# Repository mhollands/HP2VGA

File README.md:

# HP2VGA

Project to replace the display on the HP1662AS logic analyser with a VGA LCD display. 

The project uses a Texas Instruments TVP7002 Video ADC to digitise the video signal, a Lattice iCE40HX8K FPGA to buffer and upscale the video, and an Analog Devices ADV7125 to output the VGA signal to an LCD monitor.

Read more detail at projects.matthollands.com

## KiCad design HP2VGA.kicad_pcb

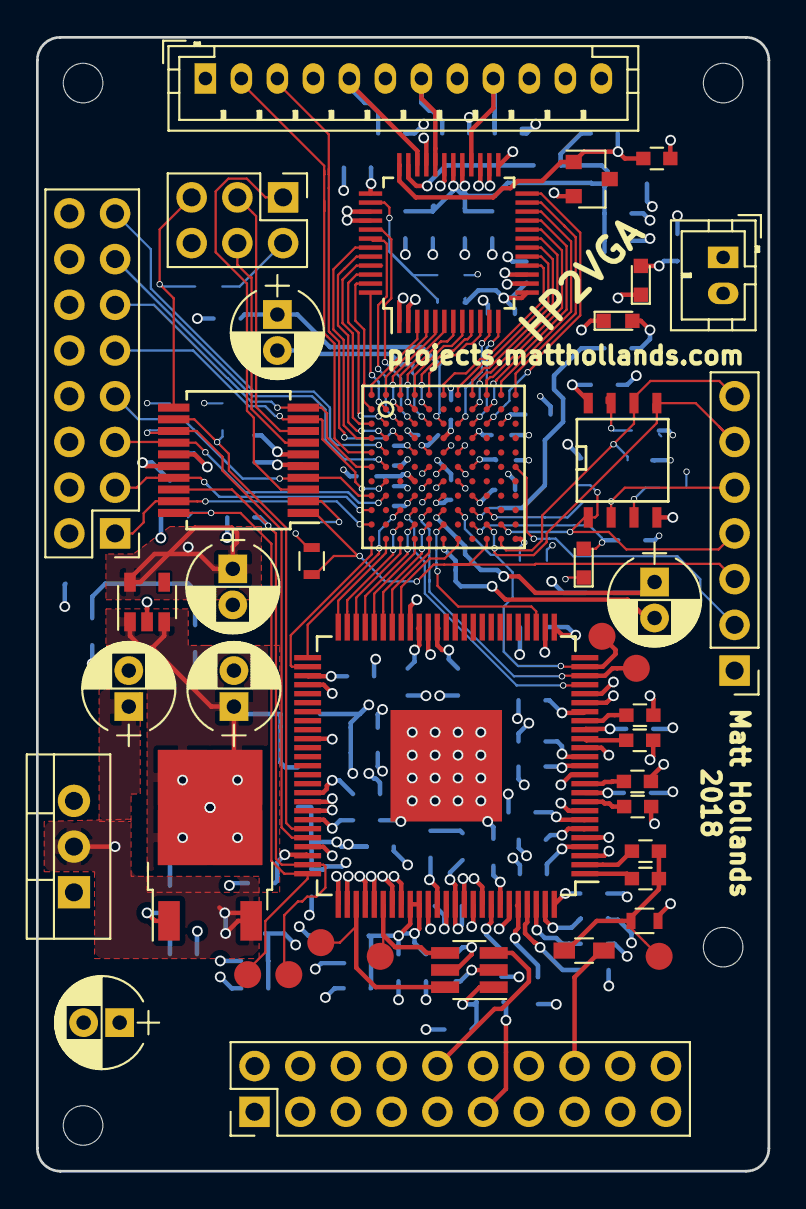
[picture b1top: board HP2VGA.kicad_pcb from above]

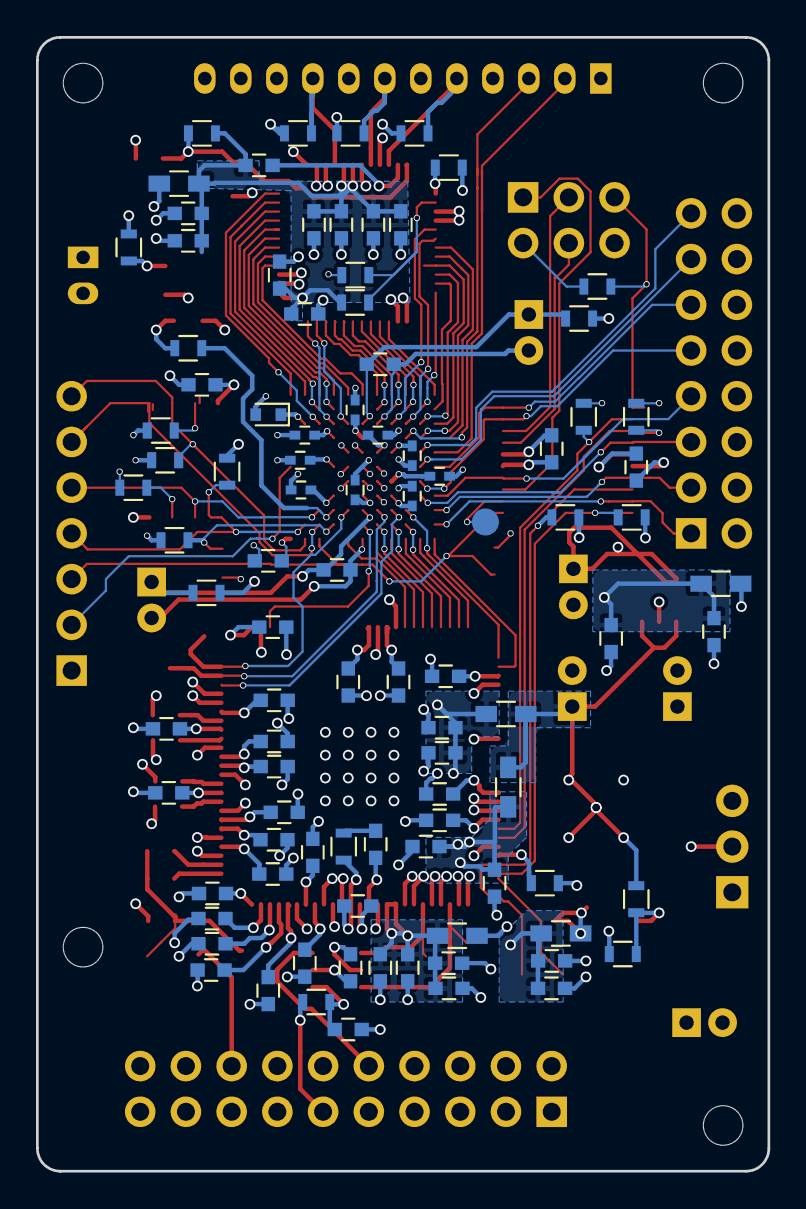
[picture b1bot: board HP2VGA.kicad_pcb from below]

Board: 4 copper layers, 40.6 x 63.0 mm, 141 parts (95 on the bottom side), 121 nets.

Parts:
C101, C102, C103, C104, C502, C504: 10uF; CP_Radial_D5.0mm_P2.00mm
C105, C107, C109, C111, C113, C115: 22uF; C_0603
C106, C108, C110, C112, C114, C116, C303: 1uF; C_0603
C201, C209: 1nF; C_0603
C202: 4.7nF; C_0603
C203, C205, C207, C208, C210, C211, C212, C213, C214, C215: 10nF; C_0603
C204: 10nf; C_0603
C206, C216, C217, C218, C219, C220, C221, C222, C223, C224, C225, C226, C227, C228, C229, C230, C231, C232, C233, C301, C304, C305, C306, C401, C402, C505, C506, C602: 0.1uF; C_0603
C302, C307, C308: 0.01uF; C_0603
C501, C503, C507, C508, C509, C510, C511, C512, C513: 0.1uF; C_0402
C601: 01uF; C_0603
CON101: AVR-ISP-6; Pin_Header_Straight_2x03_Pitch2.54mm
D101, D102, D501: LED; LED_0603
D502: CDBU0520; D_SOD-523
IC401: ATTINY87-AX; SSOP-20_5.3x7.2mm_Pitch0.65mm
L101, L102, L103, L104, L105, L106, L201: L_Small; R_0603_HandSoldering
P101: CONN_02X10; Pin_Header_Straight_2x10_Pitch2.54mm
P102: CONN_01X07; Pin_Header_Straight_1x07_Pitch2.54mm
P103: CONN_02X08; Pin_Header_Straight_2x08_Pitch2.54mm
P104: CONN_01X12; JST_PH_B12B-PH-K_12x2.00mm_Straight
P105: CONN_01X02; JST_PH_B2B-PH-K_02x2.00mm_Straight
P106, P107, P108, P109: CONN_01X01; MountingHole_2.2mm_M2
R101: 520; R_0603
R102, R302: 1k; R_0603
R103, R104: 0R; R_0603
R105, R106: 300R; R_0603
R201: 330; R_0603
R202: 75; R_0603
R203, R205, R208, R401, R402: 2k2; R_0603
R207: 1.5k; R_0603
R301: 530R; R_0603
R303, R304, R305: 75R; R_0603
R403: 4k7; R_0603
R501, R502: 100R; R_0603
R503: 649; R_0603
R504, R601, R602, R603, R604: 10k; R_0603
TP101, TP102: TEST; Measurement_Point_Round-SMD-Pad_Small
TP201: VIDEO; Measurement_Point_Round-SMD-Pad_Small
TP202: HSYNC; Measurement_Point_Round-SMD-Pad_Small
TP203: VSYNC; Measurement_Point_Round-SMD-Pad_Small
TP401: SERIAL_DEBUG; Measurement_Point_Round-SMD-Pad_Small
TP402: SDA; Measurement_Point_Round-SMD-Pad_Small
TP403: SCL; Measurement_Point_Round-SMD-Pad_Small
U101: LD1117V33; TO-220-3_Vertical
U102: NCP1117DTAG; TO-252-2
U103: TLV73312PDBVT; SOT-23-5
U201: SN74LVC2G17; SOT-23-6_Handsoldering
U202: TVP7002; TQFP-100_14x14mm_Pitch0.5mm-PowerPad
U301: ADV7125KSTZ50; LQFP-48_7x7mm_Pitch0.5mm
U302: AD1580ARTZ-REEL7; SOT-23
U501: iCE40HX8K-BG121; BGA-121-0.8mm
U601: Winbond W25Q80JV; SOIC-8-N

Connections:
+1V2: C104.1, C510.1, C511.1, C512.1, C513.1, R501.2, R502.2, U103.5, U501.D4, U501.D8, U501.H4, U501.H8
+1V9: C103.1, L101.1, L102.1, L103.1, R102.2, U102.2, U103.1, U103.3
+1V9A: C105.1, C106.1, C221.1, C222.1, C223.1, C224.1, L101.2, U202.4, U202.6, U202.7, U202.19
+1V9D: C109.1, C110.1, C219.1, C220.1, L103.2, U202.39, U202.69
+1V9PLL: C107.1, C108.1, C217.1, C218.1, L102.2, U202.84, U202.85
+3V3: C102.1, C401.1, C402.1, C501.1, C503.1, C507.1, C508.1, C509.1, C601.1, C602.1, CON101.2, D502.2, IC401.5, IC401.15, L104.1, L105.1, L106.1, R105.1, R401.1, R402.1, R403.2, R503.1, R504.1, R601.1, R602.2, R603.1, R604.1, U101.2, U102.3, U501.D6, U501.E4, U501.F8, U501.G4, U501.H6, U501.L11, U601.8
+3V3A0: C111.1, C112.1, C225.1, C226.1, C227.1, C228.1, C233.1, L104.2, U201.5, U202.13, U202.14, U202.93, U202.94
+3V3A1: C113.1, C114.1, C301.1, C302.1, C304.1, C305.1, C306.1, C307.1, C308.1, L105.2, R104.1, R302.1, U301.13, U301.29, U301.30
+3V3D0: C115.1, C116.1, C229.1, C230.1, C231.1, C232.1, L106.2, U202.26, U202.41, U202.53, U202.66
+12V: C101.1, P101.2, P101.5, P101.7, P101.9, P101.12, P105.2, U101.3
/FPGA/ADV_BLANK: U301.11, U501.C7
/FPGA/ADV_CLK: U301.24, U501.C9
/FPGA/ADV_SYNC: U301.12, U501.C8
/FPGA/B0: U301.16, U501.A6
/FPGA/B1: U301.17, U501.A7
/FPGA/B2: U301.18, U501.A8
/FPGA/B3: U301.19, U501.B8
/FPGA/B4: U301.20, U501.A9
/FPGA/B5: U301.21, U501.B9
/FPGA/B6: U301.22, U501.A10
/FPGA/B7: U301.23, U501.A11
/FPGA/CLK_EXT: P102.2, U501.F11
/FPGA/CLK_IN: U202.28, U501.K6
/FPGA/DEBUG6: P103.13, U501.F2
/FPGA/DEBUG7: P103.15, U501.E2
/FPGA/DONE: D501.2, R503.2, U501.K8
/FPGA/FIDOUT_IN: U202.22, U501.J4
/FPGA/FRAME_LED: R106.1, U501.J8
/FPGA/G0: U301.3, U501.A1
/FPGA/G1: U301.4, U501.A2
/FPGA/G2: U301.5, U501.B3
/FPGA/G3: U301.6, U501.A3
/FPGA/G4: U301.7, U501.B4
/FPGA/G5: U301.8, U501.A4
/FPGA/G6: U301.9, U501.B5
/FPGA/G7: U301.10, U501.A5
/FPGA/HSYNC_IN: TP101.1, U202.24, U501.J7
/FPGA/PROG_SCK: P102.7, R601.2, U501.L10, U601.6
/FPGA/PROG_SDI: P102.5, U501.J9, U601.2
/FPGA/PROG_SDO: P102.6, U501.K9, U601.5
/FPGA/PROG_SS: P102.4, R603.2, U501.K10, U601.1
/FPGA/R0: U301.41, U501.C4
/FPGA/R1: U301.42, U501.C3
/FPGA/R2: U301.43, U501.D1
/FPGA/R3: U301.44, U501.D2
/FPGA/R4: U301.45, U501.C1
/FPGA/R5: U301.46, U501.C2
/FPGA/R6: U301.47, U501.B1
/FPGA/R7: U301.48, U501.B2
/FPGA/VSYNC_IN: TP102.1, U202.23, U501.J5
/HSYNC_IN_A: P101.10, U201.3
/RX/G_0: U202.52, U501.L1
/RX/G_1: U202.51, U501.J3
/RX/G_2: U202.50, U501.L2
/RX/G_3: U202.49, U501.K3
/RX/G_4: U202.48, U501.L3
/RX/G_5: U202.47, U501.K4
/RX/G_6: U202.46, U501.L4
/RX/G_7: U202.45, U501.K5
/RX/G_8: U202.44, U501.L5
/RX/G_9: U202.43, U501.L7
/RX/HSYNC_BUFF: TP202.1, U201.4, U202.81
/RX/I2C_SCL: IC401.18, R402.2, TP403.1, U202.74
/RX/I2C_SDA: IC401.20, R401.2, TP402.1, U202.75
/RX/TVP_PWDN: IC401.12, R205.1, U202.70
/RX/TVP_RESET: IC401.13, R203.1, U202.71
/RX/VIDEO_L: C206.2, C209.2, L201.2, R202.1, TP201.1
/RX/VSYNC_BUFF: TP203.1, U201.6, U202.78
/TX/BLUE: P104.9, R305.1, U301.28
/TX/GREEN: P104.7, R304.1, U301.32
/TX/HSYNC_IN: P104.3, U501.D3
/TX/PSAVE: R103.2, R104.2, U301.38
/TX/RED: P104.5, R303.1, U301.34
/TX/VSYNC_IN: P104.2, U501.E1
/TX/Vref: C303.1, R302.2, U301.36, U302.1
/VIDEO_IN: L201.1, P101.16
/VSYNC_IN_A: P101.11, R201.2
/uC/FPGA_FB0: IC401.19, P103.1, U501.K1
/uC/FPGA_FB1: IC401.17, P103.3, U501.J1
/uC/FPGA_FB2: IC401.14, P103.5, U501.H2
/uC/FPGA_FB3: IC401.4, P103.7, U501.H1
/uC/FPGA_FB4: IC401.9, P103.9, U501.G2
/uC/FPGA_FB5: IC401.10, P103.11, U501.F1
/uC/FPGA_RESET: IC401.1, P102.3, R504.2, U501.L9
/uC/ISP_MISO: CON101.1, IC401.3
/uC/ISP_MOSI: CON101.4, IC401.7
/uC/ISP_RESET: CON101.5, IC401.11, R403.1
/uC/ISP_SCK: CON101.3, IC401.8
GND: C101.2, C102.2, C103.2, C104.2, C105.2, C106.2, C107.2, C108.2, C109.2, C110.2, C111.2, C112.2, C113.2, C114.2, C115.2, C116.2, C201.2, C203.2, C204.2, C205.2, C207.2, C208.2, C210.2, C211.2, C212.2, C213.2, C214.2, C215.2, C217.2, C218.2, C219.2, C220.2, C221.2, C222.2, C223.2, C224.2, C225.2, C226.2, C227.2, C228.2, C229.2, C230.2, C231.2, C232.2, C233.2, C301.2, C302.2, C303.2, C305.2, C306.2, C307.2, C308.2, C401.2, C402.2, C501.2, C503.2, C507.2, C508.2, C509.2, C510.2, C511.2, C512.2, C513.2, C601.2, C602.2, CON101.6, D101.1, D102.1, D501.1, IC401.6, IC401.16, P101.3, P101.4, P101.6, P101.8, P101.13, P101.14, P101.15, P101.17, P101.19, P102.1, P103.2, P103.4, P103.6, P103.8, P103.10, P103.12, P103.14, P103.16, P104.1, P104.4, P104.6, P104.8, P104.10, P105.1, P106.1, P107.1, P108.1, P109.1, R101.2, R103.1, R202.2, R203.2, R205.2, R208.2, R301.1, R303.2, R304.2, R305.2, U101.1, U103.2, U201.2, U202.3, U202.5, U202.8, U202.12, U202.15, U202.20, U202.21, U202.27, U202.40, U202.42, U202.54, U202.60, U202.67, U202.68, U202.72, U202.76, U202.77, U202.79, U202.80, U202.82, U202.83, U202.86, U202.90, U202.91, U202.92, U202.95, U202.101, U301.1, U301.2, U301.14, U301.15, U301.25, U301.26, U301.27, U301.31, U301.33, U301.39, U301.40, U302.2, U501.E5, U501.E6, U501.E7, U501.F5, U501.F6, U501.F7, U501.G5, U501.G6, U501.G7, U501.H5, U601.4
unnamed: C201.1, R201.1, U201.1
unnamed: C202.1, U202.88
unnamed: C202.2, R207.2, U202.89
unnamed: C203.1, U202.9
unnamed: C204.1, U202.11
unnamed: C205.1, U202.98
unnamed: C206.1, U202.2
unnamed: C207.1, U202.17
unnamed: C208.1, U202.97
unnamed: C209.1, U202.1
unnamed: C210.1, U202.10
unnamed: C211.1, U202.96
unnamed: C212.1, U202.100
unnamed: C213.1, U202.16
unnamed: C214.1, U202.18
unnamed: C215.1, U202.99
unnamed: C216.1, U202.87
unnamed: C216.2, R207.1
unnamed: C304.2, U301.35
unnamed: C502.1, C505.1, R501.1, U501.J6
unnamed: C502.2, C505.2, U501.L6
unnamed: C504.1, C506.1, R502.1, U501.C6
unnamed: C504.2, C506.2, U501.C5
unnamed: D101.2, R105.2
unnamed: D102.2, R106.2
unnamed: D502.1, U501.C10
unnamed: IC401.2, TP401.1
unnamed: R101.1, R102.1, U102.1
unnamed: R208.1, U202.73
unnamed: R301.2, U301.37
unnamed: R602.1, U601.3
unnamed: R604.2, U601.7

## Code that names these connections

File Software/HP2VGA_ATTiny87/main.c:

/*
 * HP2VGA_ATTiny87.c
 *
 * Created: 29/08/2018 21:21:04
 * Author : Matt
 */ 

#define F_CPU 8000000U

#include <stdbool.h>
#include <avr/io.h>
#include <util/delay.h>
#include <avr/interrupt.h>
#include "usiTwiMaster.h"

void TVP_PWDN(bool);
void TVP_RESET(bool);

#define TVP_W 0xB8
#define TVP_R 0xB9
#define TVP_CHIP_REV 0x00
#define TVP_HPLL_DIV_MSB 0x01
#define TVP_HPLL_DIV_LSB 0x02
#define TVP_HPLL_CTRL 0x03
#define TVP_HPLL_PHASE 0x04
#define TVP_CLAMP_START 0x05
#define TVP_CLAMP_WIDTH 0x06
#define TVP_GREEN_FINE_OFFSET 0x0C
#define TVP_SYNC_CTRL1 0x0E
#define TVP_HPLL_PRECOAST 0x12
#define TVP_SYNC_DETECT_STATUS 0x14
#define TVP_MISC_CTRL2 0x17
#define TVP_MISC_CTRL3 0x18
#define TVP_MISC_CTRL4 0x22
#define TVP_ALC_EN 0x26
#define TVP_POWER_CTRL 0x2B
#define TVP_SYNC_BYPASS 0x36
#define TVP_LPFl_STATUS 0x37
#define TVP_LPFh_STATUS 0x38
#define TVP_CPLl_STATUS 0x39
#define TVP_CPLh_STATUS 0x3A
#define TVP_HSYNC_WIDTH 0x3B
#define TVP_VSYNC_WIDTH 0x3C
#define TVP_1ST_COEF 0x4A

//800 pixels per line. hsync is 64. FP is 136. BP is 24.
//417 lines per frame. vsync is 3. FP is 25. BP is 11.
uint8_t reg_setting[66] = {	TVP_W, 0x00, 0x00, 0x64, 0x00, 0x20, 0x11, 0x01, 0x30, 0x51, 0x00, 0x90, 0x00, 0x40, 0x78, 0x80, 0x52, 0x2E, 0x5D, 0x20, 0x03, 0x03, 0x00, 0x04, 0x11,
							0x12, 0x01, 0x00, 0xC2, 0x87, 0x07, 0x00, 0x10, 0x10, 0x10, 0x00, 0x06, 0x00, 0x00, 0x00, 0x00, 0x00, 0x53, 0x08, 0x07, 0x85, 0x50, 0x00,
							0x80, 0x8c, 0x04, 0x18, 0x18, 0x60, 0x03, 0x10, 0x00, 0x00, 0x00, 0x00, 0x00, 0x00, 0x00, 0x03, 0x04, 0x0F};

//uint8_t reg_setting[66] = {	TVP_W, 0x00, 0x00, 0x64, 0x00, 0x20, 0x01, 0x01, 0x30, 0x51, 0x00, 0x90, 0x00, 0./x40, 0x78, 0x80, 0x52, 0x2E, 0x5D, 0x20, 0x03, 0x03, 0x00, 0x04, 0x11,
//	0x12, 0x01, 0x00, 0xC2, 0x87, 0x07, 0x00, 0x10, 0x10, 0x10, 0x00, 0x06, 0x00, 0x00, 0x00, 0x00, 0x00, 0x53, 0x08, 0x07, 0x85, 0x50, 0x00,
//0x80, 0x8c, 0x04, 0x18, 0x18, 0x60, 0x03, 0x10, 0x00, 0x00, 0x00, 0x00, 0x00, 0x00, 0x00, 0x03, 0x04, 0x0F};

uint8_t msg_w_phase[3] = {TVP_W,TVP_HPLL_PHASE, 0x01};
uint8_t msg_r_chiprev[4] = {TVP_W,TVP_CHIP_REV,TVP_R, 0xFF};

int main(void)
{
	sei();
	//DDRB |= 0x08; //Set FPGA_FB1 as output (PB3)
	DDRB |= 0x20; //Set TVP_RESET as output (PB5)
	DDRB |= 0x40; //Set TVP_PWDN as output (PB6)
	PORTB |= 0x05; //Set SDA and SCL as outputs (PB0/PB2)
	//DDRA |= 0x01; //Set FPGA_RESET as output (PA0)

	TVP_RESET(true); //Put TVP into reset
	//PORTA &= ~0x01; //Put the FPGA into reset
	
	_delay_ms(1000); //(TVP must be held in reset for 5ms after power up)
	
	TVP_RESET(false); //Bring TVP out of reset
	//PORTA |= 0x01; //Bring FPGA back out of reset	
	
	_delay_ms(100); //No I2C traffic for 1us after reset is released
	//TVP_PWDN(true); // Put TVP into power down
    
	usiTwiMasterInitialize();
	usiTwiStartTransceiverWithData(reg_setting, 66);
	uint8_t phase_options[2] = {0x11, 0x91};
	uint8_t selected_phase = 0;
    while (1) 
    {
		_delay_ms(16);
		if((PINB & 0x02) == 0x02)
		{
			msg_w_phase[2] = phase_options[(selected_phase & 0x01)];
			selected_phase++;
			usiTwiStartTransceiverWithData(msg_w_phase, 3);
		}
// 		_delay_ms(5000);
// 		msg_w_phase[2] = 0x91;
// 		usiTwiStartTransceiverWithData(msg_w_phase, 3);
// 		_delay_ms(5000);
// 		msg_w_phase[2] = 0x11;
// 		usiTwiStartTransceiverWithData(msg_w_phase, 3);
		//phase++;
		//if(phase > 31)
		//{
		//	phase = 0;
		//}
    }
}

void TVP_RESET(bool enable)
{
	if(enable)
	{
		PORTB &= ~0x20; //Put TVP into reset
		return;
	}
	PORTB |= 0x20; //Bring TVP out of reset
}

void TVP_PWDN(bool enable)
{
	if(enable)
	{
		PORTB |= 0x40; // Put TVP into power down mode
		return;
	}
	PORTB &= ~0x40; //Bring TVP out of power down mode
}

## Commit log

2018-09-09 everything so far
2018-09-09 small changes
2018-09-09 created RX module and moved 1HZ Pulse into it
2018-09-09 added O_COUNTER module and moved 1HZ Pulse stuff into that
2018-09-09 improved VISIBLE comparison in VGA_COUNTER
2018-09-09 in a working state
2018-09-09 changed HS and VS outputs to be reg instead of wire. This got rid of a weird glitch on HS, however I need to rethink timing as a result
2018-09-14 TX and RX accessing RAM. Sync not working.
2018-09-15 stable video output but wrong resolution and looks a bit dodgy
2018-09-23 use 2nd pll to get a more desirable TX frequency of 48.96MHz. Also introduced 'smooth sync' where synchronisation will only start when the two video signals are already in sync. Now the display can l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
2018-09-23 working on getting good display. strange notches in image approximately every 80 lines. Probably not sure to RX. Therefore probably TX. HW is also very sensitive to changes in inputs and can just bre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
2018-09-29 FRAME ACUTALLY LOOKS GOOD. Hold violation on TVP inputs. Solution is to set the TVP to output data on the falling edge rather than the rising edge. This splits the time between setup and hold rather 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
2018-09-30 added buffers on all TVP inputs
2018-10-07 added RX_SYNC_WATCHDOG module that looks for when HSYNC pll is misaligned. This then raises FPGA_FB0 pin. ATtiny monitors this pin and progresses through phase options on TVP until phase is corrected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
2018-10-07 tidy up
2018-10-29 final touches and comments
2018-10-29 remove dunused cad
2018-10-29 Move kicad stuff into it's own folder
2020-05-30 add shelf
